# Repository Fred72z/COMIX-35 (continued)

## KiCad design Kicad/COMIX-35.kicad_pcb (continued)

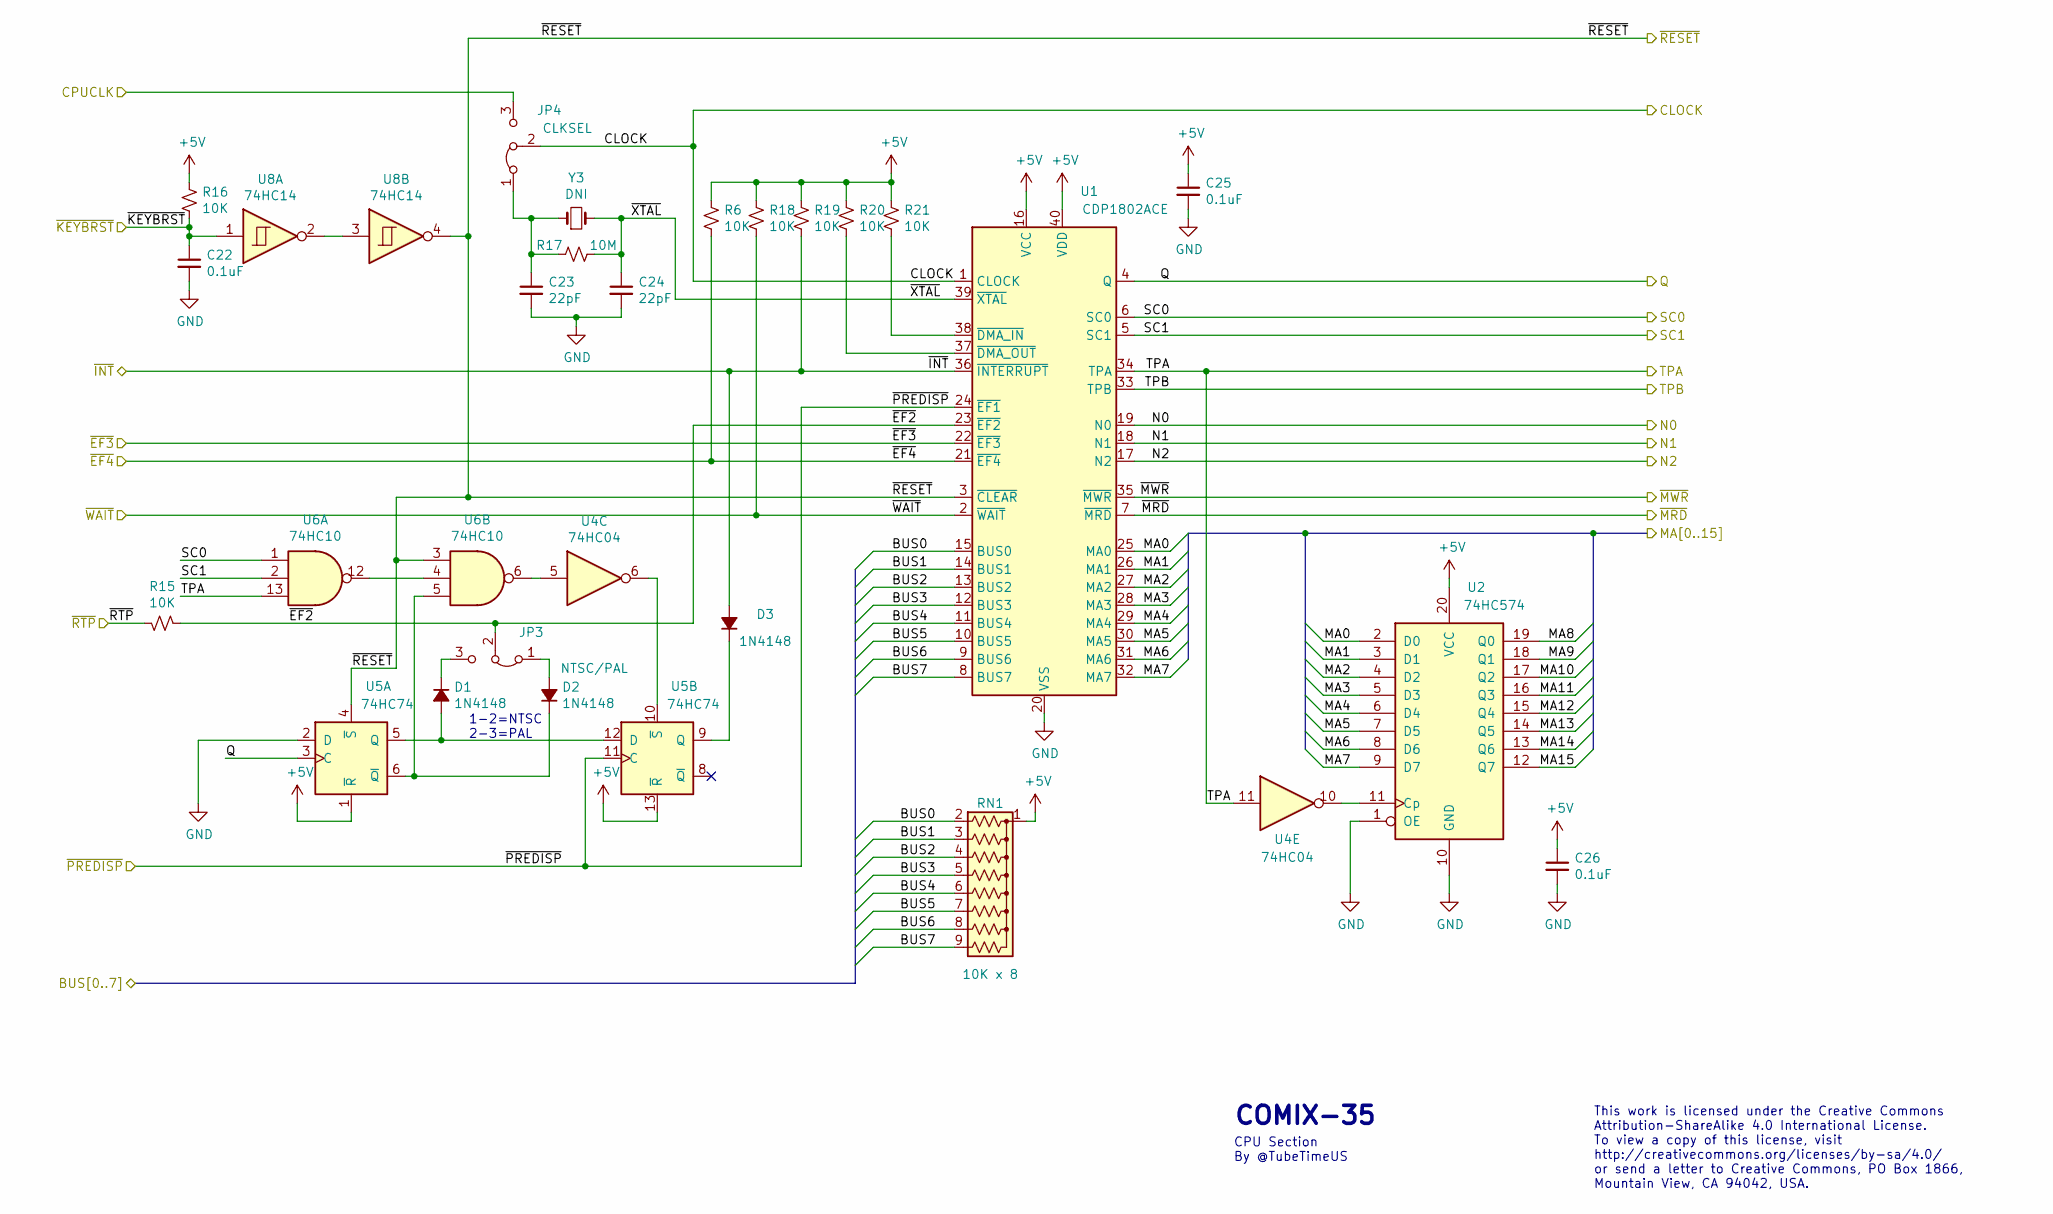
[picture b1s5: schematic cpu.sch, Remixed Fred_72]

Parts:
C22, C25, C26: 0.1uF; CAPAC200; Mouser 581-SA105E104M
C23, C24: 22pF; CAPAC200; Mouser 810-FG28C0G2A220JNT0
D1, D2, D3: 1N4148; DIOA500; Mouser 512-1N4148
JP3: NTSC/PAL; Pin_Header_Straight_1x03_Pitch2.54mm
JP4: CLKSEL; Pin_Header_Straight_1x03_Pitch2.54mm
R6, R15, R16, R18, R19, R20, R21: 10K; RESA500; Mouser 603-CFR-25JB-52-10K
R17: 10M; RESA500; Mouser 603-CFR-25JT-52-10M
RN1: 10K x 8; Pin_Header_Straight_1x09_Pitch2.54mm; Mouser 652-4609X-1LF-10K
U1: CDP1802ACE; DIP-40_W15.24mm
U2: 74HC574; DIP-20_W7.62mm; Mouser 595-SN74HC574N
U4: 74HC04; DIP-14_W7.62mm; Mouser 595-SN74HC04N
U5: 74HC74; DIP-14_W7.62mm; Mouser 595-SN74HC74N
U6: 74HC10; DIP-14_W7.62mm; Mouser 595-SN74HC10N
U8: 74HC14; DIP-14_W7.62mm; Mouser 595-SN74HC14N
Y3: DNI; Crystal_HC49-4H_Vertical; Mouser DNI

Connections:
+5V: C25.1, C26.1, R6.2, R16.2, R18.2, R19.2, R20.2, R21.2, RN1.1 (common), U1.16 (VCC), U1.40 (VDD), U2.20 (VCC), U5.1 (~R), U5.13 (~R); also elsewhere on the board
/BUS0: RN1.2 (R1), U1.15 (BUS0); also elsewhere on the board
/BUS1: RN1.3 (R2), U1.14 (BUS1); also elsewhere on the board
/BUS2: RN1.4 (R3), U1.13 (BUS2); also elsewhere on the board
/BUS3: RN1.5 (R4), U1.12 (BUS3); also elsewhere on the board
/BUS4: RN1.6 (R5), U1.11 (BUS4); also elsewhere on the board
/BUS5: RN1.7 (R6), U1.10 (BUS5); also elsewhere on the board
/BUS6: RN1.8 (R7), U1.9 (BUS6); also elsewhere on the board
/BUS7: RN1.9 (R8), U1.8 (BUS7); also elsewhere on the board
/CLOCK: JP4.2 (C), U1.1 (CLOCK); also elsewhere on the board
/CPUCLK: JP4.3 (B); also elsewhere on the board
/MA0: U1.25 (MA0), U2.2 (D0); also elsewhere on the board
/MA1: U1.26 (MA1), U2.3 (D1); also elsewhere on the board
/MA2: U1.27 (MA2), U2.4 (D2); also elsewhere on the board
/MA3: U1.28 (MA3), U2.5 (D3); also elsewhere on the board
/MA4: U1.29 (MA4), U2.6 (D4); also elsewhere on the board
/MA5: U1.30 (MA5), U2.7 (D5); also elsewhere on the board
/MA6: U1.31 (MA6), U2.8 (D6); also elsewhere on the board
/MA7: U1.32 (MA7), U2.9 (D7); also elsewhere on the board
/MA14: U2.13 (Q6); also elsewhere on the board
/N0: U1.19 (N0); also elsewhere on the board
/N1: U1.18 (N1); also elsewhere on the board
/N2: U1.17 (N2); also elsewhere on the board
/Q: U1.4 (Q), U5.3 (C); also elsewhere on the board
/SC0: U1.6 (SC0), U6.1; also elsewhere on the board
/SC1: U1.5 (SC1), U6.2; also elsewhere on the board
/TPA: U1.34 (TPA), U4.11, U6.13; also elsewhere on the board
/TPB: U1.33 (TPB); also elsewhere on the board
/cpu/MA8: U2.19 (Q0); also elsewhere on the board
/cpu/MA9: U2.18 (Q1); also elsewhere on the board
/cpu/MA10: U2.17 (Q2); also elsewhere on the board
/cpu/MA11: U2.16 (Q3); also elsewhere on the board
/cpu/MA12: U2.15 (Q4); also elsewhere on the board
/cpu/MA13: U2.14 (Q5); also elsewhere on the board
/cpu/MA15: U2.12 (Q7); also elsewhere on the board
/cpu/~EF2: JP3.2 (C), R15.2, U1.23 (~EF2)
/cpu/~XTAL: C24.1, R17.2, U1.39 (~XTAL), Y3.2
/~EF3: U1.22 (~EF3); also elsewhere on the board
/~EF4: R6.1, U1.21 (~EF4); also elsewhere on the board
/~INT: D3.2 (A), R19.1, U1.36 (~INTERRUPT); also elsewhere on the board
/~KBDRST: C22.1, R16.1, U8.1; also elsewhere on the board
/~MRD: U1.7 (~MRD); also elsewhere on the board
/~MWR: U1.35 (~MWR); also elsewhere on the board
/~PREDISP: U1.24 (~EF1), U5.11 (C); also elsewhere on the board
/~RESET: U1.3 (~CLEAR), U5.4 (~S), U6.3, U8.4; also elsewhere on the board
/~RTP: R15.1; also elsewhere on the board
/~WAIT: R18.1, U1.2 (~WAIT); also elsewhere on the board
GND: C22.2, C23.2, C24.2, C25.2, C26.2, U1.20 (VSS), U2.1 (OE), U2.10 (GND), U5.2 (D); also elsewhere on the board
unnamed: C23.1, JP4.1 (A), R17.1, Y3.1
unnamed: D1.1 (K), JP3.3 (B)
unnamed: D1.2 (A), U5.5 (Q), U5.12 (D)
unnamed: D2.1 (K), U5.6 (~Q), U6.5
unnamed: D2.2 (A), JP3.1 (A)
unnamed: D3.1 (K), U5.9 (Q)
unnamed: R20.1, U1.37 (~DMA_OUT)
unnamed: R21.1, U1.38 (~DMA_IN)
unnamed: U2.11 (Cp), U4.10
unnamed: U4.5, U6.6
unnamed: U4.6, U5.10 (~S)
unnamed: U6.4, U6.12
unnamed: U8.2, U8.3

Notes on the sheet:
1-2=NTSC 2-3=PAL
This work is licensed under the Creative Commons Attribution-ShareAlike 4.0 International License. To view a copy of this license, visit http://creativecommons.org/licenses/by-sa/4.0/ or send a letter to Creative Commons, PO Box 1866, Mountain View, CA 94042, USA.
COMIX-35
CPU Section By @TubeTimeUS

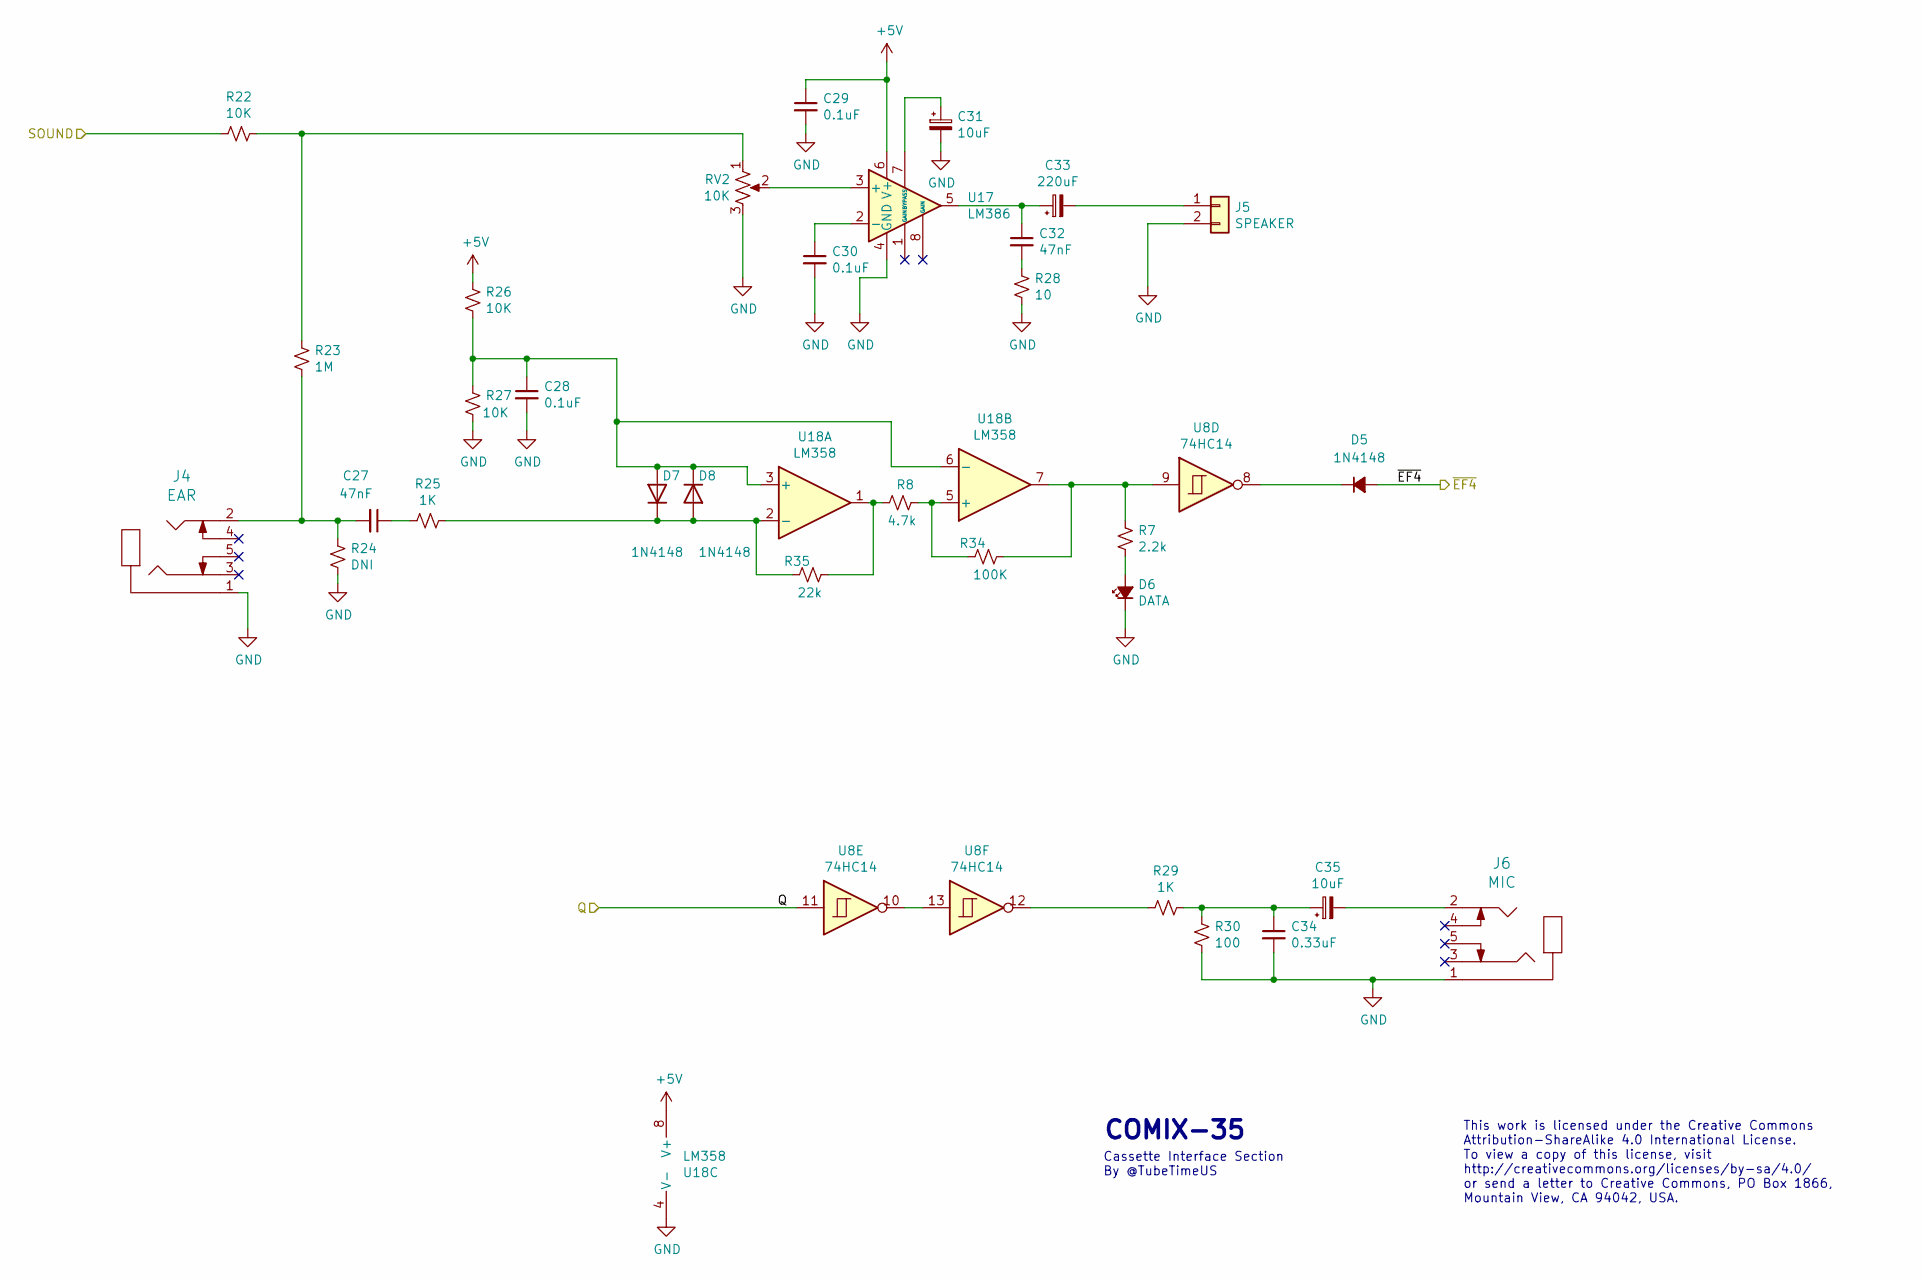
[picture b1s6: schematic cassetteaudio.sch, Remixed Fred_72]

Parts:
C27: 47nF; CAPAC200; Mouser 810-FG24X7R1H334KNT6
C28: 0.1uF; CAPAC200; Mouser 810-FG28X7R1H102KNT6
C29, C30: 0.1uF; CAPAC200; Mouser 581-SA105E104M
C31, C35: 10uF; CAPAE250P630X1100; Mouser 667-ECA-1CM100I
C32: 47nF; CAPAC200; Mouser 810-FA28X7R1H47300
C33: 220uF; CAPAE250P630X1100; Mouser 647-UVY1E221MED1TD
C34: 0.33uF; CAPAC200; Mouser 810-FG28X7R1H334KRT0
D5: 1N4148; DIOA500; Mouser 512-1N4148
D6: DATA; LED_D5.0mm; Mouser 859-LTL-4213
D7, D8: 1N4148; D_DO-35_SOD27_P7.62mm_Horizontal
J4: EAR; CUI_SJ1-353XN; Mouser 490-SJ1-3533NG
J5: SPEAKER; Pin_Header_Straight_1x02_Pitch2.54mm
J6: MIC; CUI_SJ1-353XN; Mouser 490-SJ1-3533NG
R7: 2.2k; RESA500; Mouser 603-CFR-25JR-52220R
R8: 4.7k; RESA500; Mouser 603-CFR-25JB-52-10K
R22, R26, R27: 10K; RESA500; Mouser 603-CFR-25JB-52-10K
R23: 1M; RESA500; Mouser 603-CFR-25JR-521M
R24: DNI; RESA500; Mouser DNI
R25, R29: 1K; RESA500; Mouser 603-CFR-25JR-521K
R28: 10; RESA500; Mouser 603-CFR-25JR-5210R
R30: 100; RESA500; Mouser 603-CFR-25JR-52100R
R34: 100K; RESA500; Mouser 603-CFR-25JB-52-10K
R35: 22k; RESA500; Mouser 603-CFR-25JB-52-10K
RV2: 10K; POT_plat_PCB; Mouser 531-PT10H-10K-S
U8: 74HC14; DIP-14_W7.62mm; Mouser 595-SN74HC14N
U17: LM386; DIP-8_W7.62mm; Mouser 926-LM386N-4/NOPB
U18: LM358; DIP-8_W7.62mm

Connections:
+5V: C29.1, R26.1, U17.6 (V+), U18.8 (V+); also elsewhere on the board
/Q: U8.11; also elsewhere on the board
/cassetteaudio/SOUND: R22.2; also elsewhere on the board
/~EF4: D5.2 (A); also elsewhere on the board
GND: C28.2, C29.2, C30.2, C31.2, C34.2, D6.1 (K), J4.1, J5.2, J6.1, R24.1, R27.2, R28.2, R30.2, RV2.3, U17.4 (GND), U18.4 (V-); also elsewhere on the board
unnamed: C27.1, R25.2
unnamed: C27.2, J4.2, R23.2, R24.2
unnamed: C28.1, D7.2 (A), D8.1 (K), R26.2, R27.1, U18.3 (+), U18.6 (-)
unnamed: C30.1, U17.2 (-)
unnamed: C31.1, U17.7 (BYPASS)
unnamed: C32.1, C33.1, U17.5
unnamed: C32.2, R28.1
unnamed: C33.2, J5.1
unnamed: C34.1, C35.1, R29.1, R30.1
unnamed: C35.2, J6.2
unnamed: D5.1 (K), U8.8
unnamed: D6.2 (A), R7.1
unnamed: D7.1 (K), D8.2 (A), R25.1, R35.2, U18.2 (-)
unnamed: R22.1, R23.1, RV2.1
unnamed: R29.2, U8.12
unnamed: R7.2, R34.1, U8.9, U18.7
unnamed: R8.1, R34.2, U18.5 (+)
unnamed: R8.2, R35.1, U18.1
unnamed: RV2.2, U17.3 (+)
unnamed: U8.10, U8.13

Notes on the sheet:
This work is licensed under the Creative Commons Attribution-ShareAlike 4.0 International License. To view a copy of this license, visit http://creativecommons.org/licenses/by-sa/4.0/ or send a letter to Creative Commons, PO Box 1866, Mountain View, CA 94042, USA.
COMIX-35
Cassette Interface Section By @TubeTimeUS

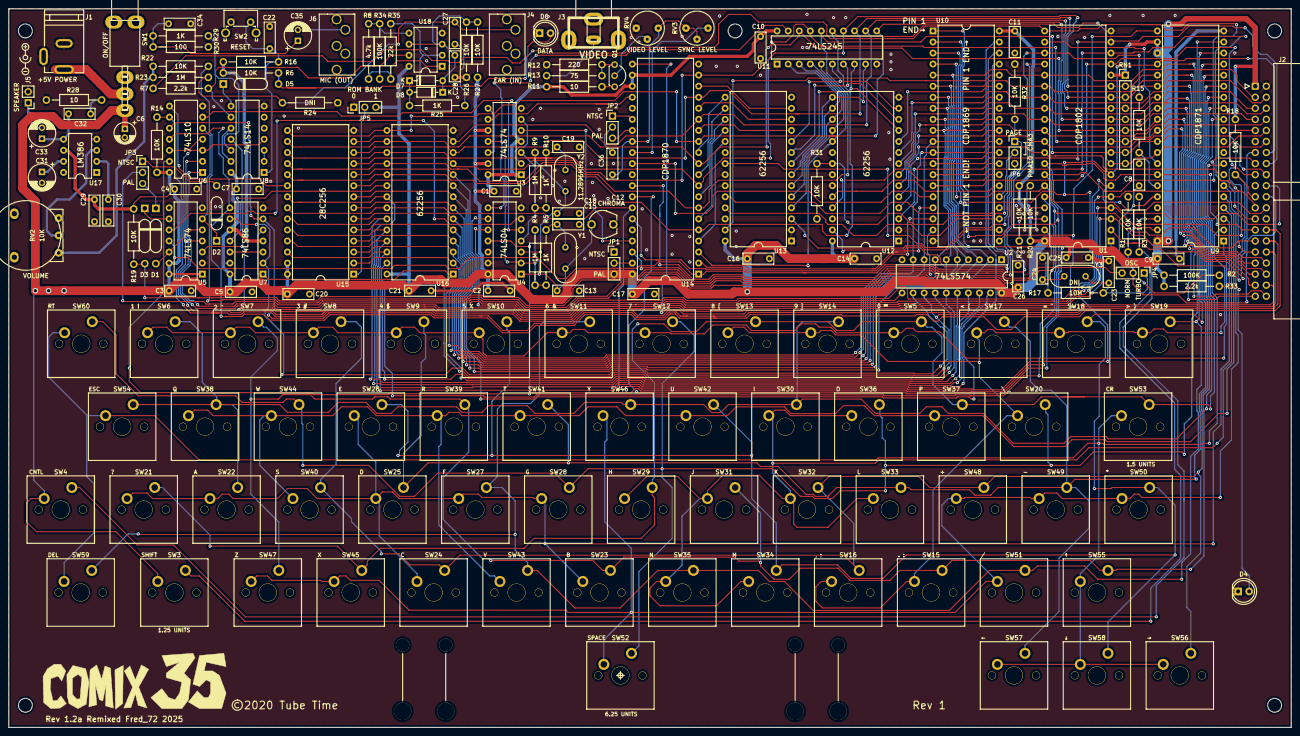
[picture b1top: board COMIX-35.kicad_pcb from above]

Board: 2 copper layers, 294.6 x 165.1 mm, 183 parts (0 on the bottom side), 170 nets.
